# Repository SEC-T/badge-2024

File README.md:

# SEC-T 0x10sion Music Synthesizer Badge kit

The SEC-T 0x10sion Music Synthesizer Badge is a kit that attendees of SEC-T 0x10sion 2024 must solder together.
It is an Arduino-compatible music synthesizer kit with:
* a touch keyboard
* built-in speaker/amp
* audio output jack (for high-quality audio)
* 5 programmable RGB LEDs

It is designed to be perfect for total beginners to learn to solder and complete successfully.

The SEC-T Synth Badge comes with a pre-programmed music synthesizer that makes way cool sounds and music and noise.
Once soldering is completed, the SEC-T Synth Badge is a really nice, portable, performing musical instrument!

The SEC-T Synth Badge kit is based on the ArduTouch music synthesizer kit by Mitch Altman / Cornfield Electronics,
which is fully Open Hardware, with a CC BY-SA 4.0 license.

The SEC-T Synth Badge makes use of a modified ArduTouch library, which is available for
programming in more super nice synthesizer features, and for making your own synthesizers.
The library comes with examples (with more to come) that serve as a nice tutorial
on how to create your own SEC-T Synth Badge synthesizers (which are Arduino sketches).

The SEC-T Synth Badge is really just an Arduino Uno clone
with the features listed above, a couple of extra buttons, and a four of pots (for playing music and controlling the sounds).
The ArduTouch Arduino Library is where the real magic comes from!

For those who want to learn more, the documentation teaches the basics of Digital Signal Processing for audio generation.

The SEC-T Synth Badge kit is fully Open Hardware, with a CC BY-SA 4.0 license.

---
## Assembly Instructions (with re-programming how-to)

_Click on the image below to open a PDF file with detailed instructions on how to assemble your SEC-T 0x10sion Music Synthesizer Badge (which also includes a how-to for re-programming your Synth Badge with a new Arduino sketch):_  
  
### Part 1 of 2 parts:

### Part 2 of 2 parts:

---
## "Quadrant" Synth Demo Videos

The Synth Badge comes pre-programmed with a synth called __Quadrant__.  
Quadrant is somewhat like a looper.  Every time you play a note it goes into the loop.  You can control the speed of the loop, and you can also make the sound warp (detune) every time through the loop.  
  
There is the default patch for Quadrant, plus 4 presets -- all 5 of these have very different sounds!  
In addition to changing the loop speed and changing the warp-factor, there are many parameters that you can play with, some of which change the sounds in subtle ways, others which change the sounds a lot.  

These demo videos give you a very small taste of the various sounds Quadrant can make. 

___NOTE__:  The demo videos use the prototype version of the SEC-T 0x10sion Music Synthesizer Badge kit._  
There are some differences between the prototype version and the badges at the event.  In particular, the two red buttons are reversed (left and right).  

__Basic Functionality of Quadrant__:  
* At power-up (or after Reset), Quadrant is in the Default Patch
* Single-Click the right red button to go up an octave
* Single-Click the left red button to go down an octave
* Double-Click the right red button and then hit one of the first four lower touch-keys to choose a preset
  * The left-most touch-key is "C" -- Scaffold
  * The next touch-key is "D" -- Farsy
  * "E" -- Teleprompt
  * "F" -- Glacial
  * "G" -- Blur
* Tap the Reset button to get the Default Patch
* The Top Pot controls the Warp-factor
* The Bottom Pot controls the speed of the loop
* Pot A controls tremelo speed
* Pot B controls tremelo depth
* Press-and-hold on the left and right red buttons will make the Red and Blue LEDs light or blink, indicating that the four Pots will now control different parameters.  
  
See the next section, "Quadrant Synth User Guide", for a complete description of all that the Quadrant Synth can do.  
  
### Default Patch (at power-up and after Reset) _-- click on the image below to play the video_

### Preset "C" -- Scaffold _-- click on the image below to play the video_

### Preset "D" -- Farsy _-- click on the image below to play the video_

### Preset "E" -- Teleprompt _-- click on the image below to play the video_

### Preset "F" -- Glacial _-- click on the image below to play the video_

### Preset "G" -- Blur _-- click on the image below to play the video_

---
## Quadrant Synth User Guide

The Synth Badge comes pre-programmed with a synth called __Quadrant__.  Quadrant is a very powerful performing musical instrument.  
_Click on the image below to learn how to play with it:_  

---
## Re-programming the Synth Badge

The Synth Badge can be re-programmed using the free Arduino software (on Windows, Linux, and MacOS).  
The end pages of the [Synth Assembly Instructions](https://github.com/user-attachments/files/16896082/SEC-T_0x10sion_badge_assembly_part_2of2.pdf) explain how to do this.  
To re-program your Synth Badge you will need to use a USB-Serial TTL adapter.  
  
The Synth Badge comes pre-programmed with the __Quadrant__ synth.  
  
There are 8 other synths that were developed for the open hardware_ArduTouch_ project (which the Synth Badge is based on), all of which will work on the SEC-T Synth Badge.  But you should be aware of the following:  
* The Synth Badge has 5 programmable RGB LEDs that the _ArduTouch_ boards do not have.  
* The __Quadrant__ synth sketch (from the Synth Badge's Github) has code for controlling the RGB LEDs, but the _ArduTouch synth sketches do not -- though this functionality can be added by you or others.  
* The Synth Badge does not have touch-keys for "A, A#, or B).
  
All of the documentation for [ArduTouch](https://cornfieldelectronics.com/cfe/projects.php#ardutouch), including the synth sketches, is available on the Cornfield Electronics website:  
https://cornfieldelectronics.com/cfe/projects.php#ardutouch  
  
Here is a list of ArduTouch synths that you can program into your Synth Badge:
* __Thick__: 4-voice sawtooth synth
* __Arpology__: Arpegiating synth
* __Beatitude__: drum sequencer with bass synth
* __Dronetic__: drone-making synth
* __Hocus__: Hammond organ (with Leslie) emulator synth
* __Mantra__: Indian-like percusion/bass/drone/melody synth
* __Xoid__: Digital-noise synth
* __ZapShot__: 8-bit video-game-sound synth

---
## A Note on the (Horrible) User Interface for the Quadrant Synth

As noted in the [Quadrant Synth User Guide](https://github.com/user-attachments/files/16901048/Quadrant_Synth_User_Guide.pdf) (see the "Quadrant Synth User Guide", above), the User Interface is really annoying.  

The following is quoted from the Quadrant Synth User Guide:  
  
&nbsp;&nbsp;&nbsp;&nbsp;&nbsp;&nbsp;_You will be annoyed at the User Interface for this synth.  Sorry about that.  The reason that it is so annoying  
&nbsp;&nbsp;&nbsp;&nbsp;&nbsp;&nbsp;is that there are so few Input/Output pins available on the microcontroller.  There were only enough I/O pins  
&nbsp;&nbsp;&nbsp;&nbsp;&nbsp;&nbsp;for 2 LED indicators, 2 Buttons, and 4 Pots._  
  
&nbsp;&nbsp;&nbsp;&nbsp;&nbsp;&nbsp;_I had to come up with a way to control all of the functionality of the Quadrant synth with only the above inputs  
&nbsp;&nbsp;&nbsp;&nbsp;&nbsp;&nbsp;and outputs.  The result is not ideal.  Yet, with some practice, you will find that your Quadrant synth is quite  
&nbsp;&nbsp;&nbsp;&nbsp;&nbsp;&nbsp;usable as a really nice performing musical instrument._  
  
&nbsp;&nbsp;&nbsp;&nbsp;&nbsp;&nbsp;_FYI:  I chose this microcontroller to be the same as the one used in an Arduino Uno:  ATmega328.  This was so  
&nbsp;&nbsp;&nbsp;&nbsp;&nbsp;&nbsp;that the project would be easy to use for beginners, easy to learn for beginners, easy to hack, and also as  
&nbsp;&nbsp;&nbsp;&nbsp;&nbsp;&nbsp;inexpensive as possible._  

---
## Schematic Diagram

_Click on the thumbnail below to to see the PDF file:_

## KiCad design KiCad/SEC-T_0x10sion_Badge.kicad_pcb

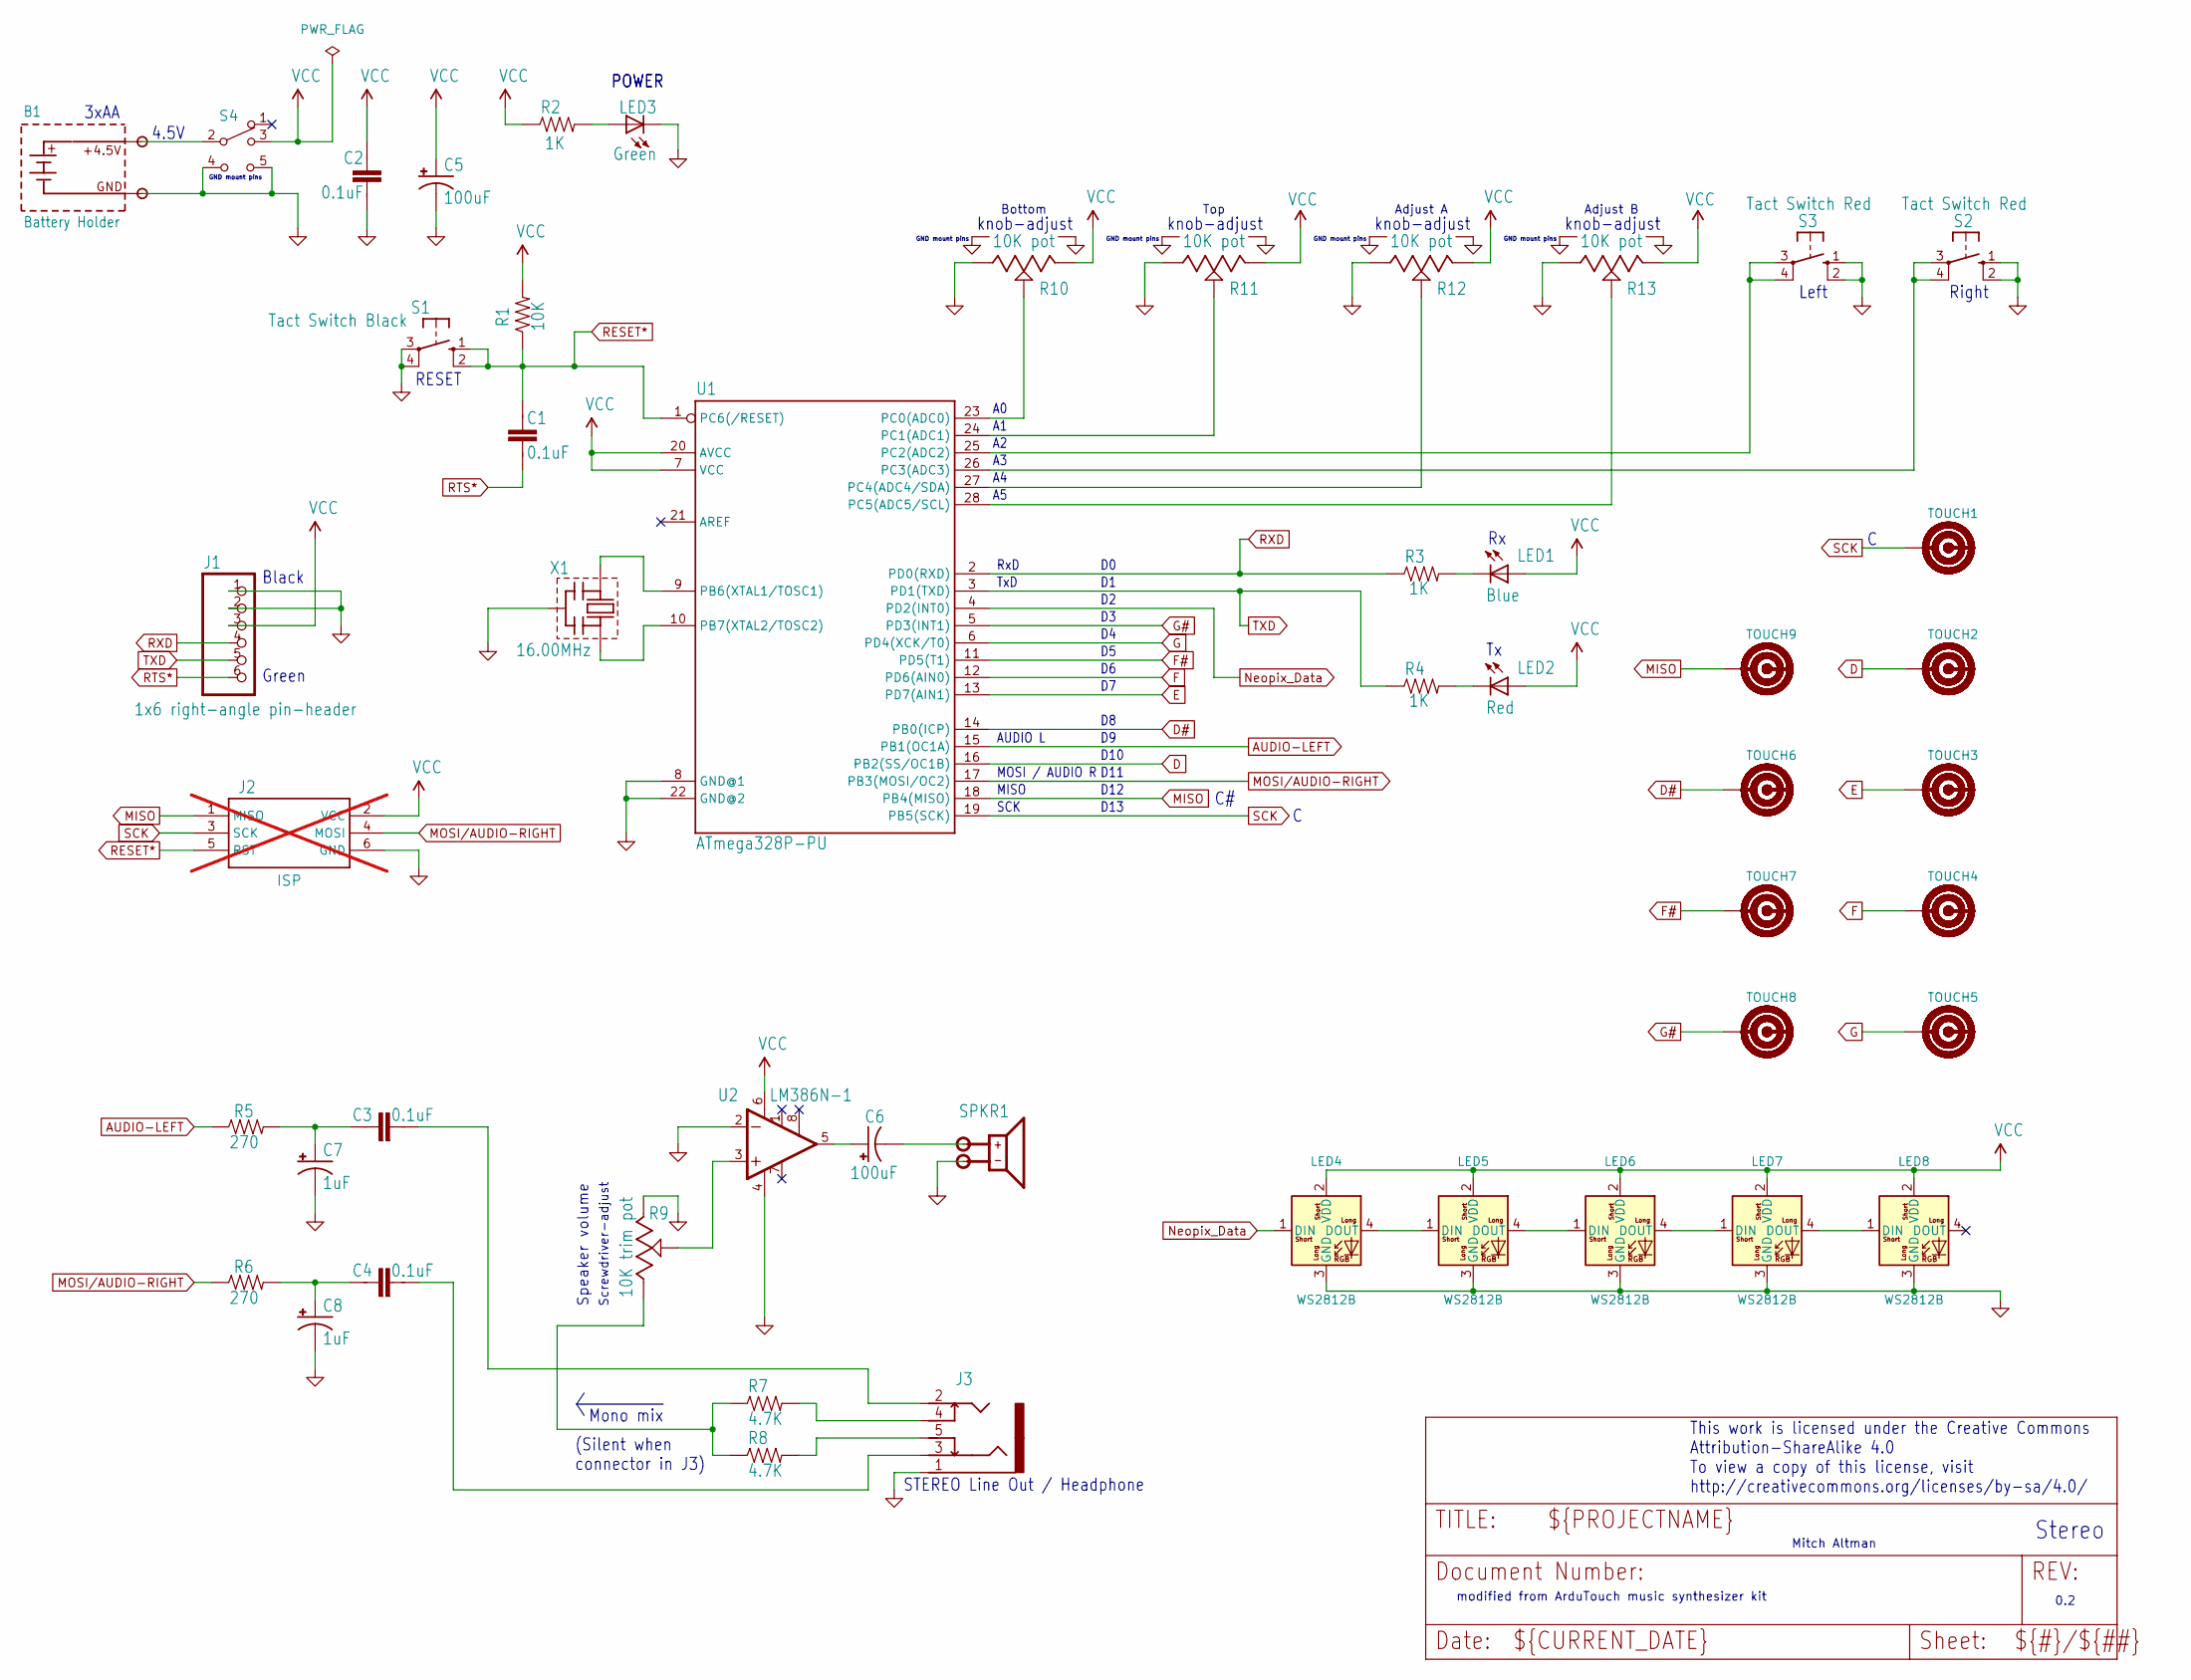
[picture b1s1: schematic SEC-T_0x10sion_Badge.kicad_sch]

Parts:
B1: Battery Holder; BatteryHolder_Eagle_Plastic_Devices_3xAA; Part # Eagle Plastic 12BH331P-GR
C1, C2, C3, C4: 0.1uF; Cap_Kemet_2.54_MLCC_through-hole; Part # KEMET C320C104M5R5TA
C5, C6: 100uF; Cap_Wurth_Electrolytic_100uF; Part # Wurth 860010473007
C7, C8: 1uF; Cap_Rubycon_Electrolytic_1uF; Part # Rubycon 450PK1MEFC6.3X11
J1: 1x6 right-angle pin-header; 1x06-pin-header_2.54mm_spacing; Part # Amphenol 10129379-906004BLF
J2: ISP; 2x3_-pin-header_2.54mm_spacing; Part # {not stuffed); not fitted
J3: STEREO-AUDIO-3.5MM-SWITCHED; 3.5mm_CUI_SJ1-3525NG_Horizontal; Part # CIU Devices SJ1-3525NG-GR
LED1: Blue; LED5MM; Part # Wurth 151051BS04000
LED2: Red; LED5MM; Part # Wurth 151051SS04000
LED3: Green; LED5MM; Part # Wurth 151051VS04000
LED4, LED5, LED6, LED7, LED8: WS2812B; LED_WS2812_5mm_Wide_Pins; Part # SparkFun COM-12986
R1: 10K; Resistor_THT_0.25W; Part # SEI Stackpole CF18JT10K0
R2, R3, R4: 1K; Resistor_THT_0.25W; Part # YAGEO CFR-25JR-52-1K
R5, R6: 270; Resistor_THT_0.25W; Part # YAGEO CFR25SJT-26-270R
R7, R8: 4.7K; Resistor_THT_0.25W; Part # YAGEO CFR25SJT-52A4K7
R9: 10K trim pot; TRIMPOT-Bourns-3306F
R10, R11, R12, R13: 10K pot; Potentiometer_TT_P120PK; Part # TT Electronics P120PK-Y25BR10K
S1: Tact Switch Black; TACTILE_SWITCH_6.3MM; Part # CUI Devices TS02-66-60-BK-260-LCR-D
S2, S3: Tact Switch Red; TACTILE_SWITCH_6.3MM; Part # Diptronics DTS-65R-V
S4: SPST; C&K_SPST_OS102011MS2QS1; Part # C&K OS102011MS2QS1
SPKR1: SPEAKER-TERMINALS; Part # DONGGUAN INGHAI ELECTRONICS GSPK2003TN-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
TOUCH1, TOUCH2, TOUCH3, TOUCH4, TOUCH5, TOUCH6, TOUCH7, TOUCH8, TOUCH9: PCB-TOUCHPAD
U1: ATmega328P-PU; DIP-28_W7.62mm_Socket
U2: LM386N-1; DIP-8_W7.62mm; Part # Texas Instruments LM386N-1/NOPB
X1: 16.00MHz; CERM_OSC_16MHz; Part # Murata CSTLS16M0X53-B0

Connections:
AUDIO-LEFT: R5.P$1 (1), U1.15 (PB1(OC1A))
D: TOUCH2.1, U1.16 (PB2(SS/OC1B))
D#: TOUCH6.1, U1.14 (PB0(ICP))
E: TOUCH3.1, U1.13 (PD7(AIN1))
F: TOUCH4.1, U1.12 (PD6(AIN0))
F#: TOUCH7.1, U1.11 (PD5(T1))
G: TOUCH5.1, U1.6 (PD4(XCK/T0))
G#: TOUCH8.1, U1.5 (PD3(INT1))
GND: B1.-, C2.2, C5.-, C7.-, C8.-, J1.1, J1.2, J2.6 (GND), J3.1 (GND), LED3.K (C), LED4.3 (GND), LED5.3 (GND), LED6.3 (GND), LED7.3 (GND), LED8.3 (GND), R9.1 (CCW), R10.1 (CCW), R10.GND, R11.1 (CCW), R11.GND, R12.1 (CCW), R12.GND, R13.1 (CCW), R13.GND, S1.3, S1.4, S2.1, S2.2, S3.1, S3.2, S4.4 (GND), S4.5 (GND), SPKR1.-, U1.8 (GND@1), U1.22 (GND@2), U2.2 (-IN), U2.4 (V-), X1.P$2 (GND)
MISO: J2.1 (MISO), TOUCH9.1, U1.18 (PB4(MISO))
MOSI/AUDIO-RIGHT: J2.4 (MOSI), R6.P$1 (1), U1.17 (PB3(MOSI/OC2))
Neopix_Data: LED4.1 (DIN), U1.4 (PD2(INT0))
unnamed: B1.+, S4.2
unnamed: C6.-, SPKR1.+
unnamed: C4.2, J3.3 (Ring)
unnamed: J3.5 (Ring_Switch), R8.P$2 (2)
unnamed: C3.2, J3.2 (Tip)
unnamed: J3.4 (Tip_Switch), R7.P$2 (2)
unnamed: LED1.K (C), R3.P$2 (2)
unnamed: LED2.K (C), R4.P$2 (2)
unnamed: LED4.4 (DOUT), LED5.1 (DIN)
unnamed: LED5.4 (DOUT), LED6.1 (DIN)
unnamed: LED6.4 (DOUT), LED7.1 (DIN)
unnamed: LED7.4 (DOUT), LED8.1 (DIN)
unnamed: LED3.A, R2.P$2 (2)
unnamed: C3.1, C7.+, R5.P$2 (2)
unnamed: C4.1, C8.+, R6.P$2 (2)
unnamed: R7.P$1 (1), R8.P$1 (1), R9.3 (CW)
unnamed: R9.2 (Wiper), U2.3 (+IN)
unnamed: R10.2 (Wiper), U1.23 (PC0(ADC0))
unnamed: R11.2 (Wiper), U1.24 (PC1(ADC1))
unnamed: R12.2 (Wiper), U1.27 (PC4(ADC4/SDA))
unnamed: R13.2 (Wiper), U1.28 (PC5(ADC5/SCL))
unnamed: U1.9 (PB6(XTAL1/TOSC1)), X1.P$1 (IN)
unnamed: U1.10 (PB7(XTAL2/TOSC2)), X1.P$3 (OUT)
unnamed: S3.3, S3.4, U1.25 (PC2(ADC2))
unnamed: S2.3, S2.4, U1.26 (PC3(ADC3))
unnamed: C6.+, U2.5 (OUT)
RESET*: C1.1, J2.5 (RST), R1.P$1 (1), S1.1, S1.2, U1.1 (PC6(/RESET))
RTS*: C1.2, J1.6
RXD: J1.4, R3.P$1 (1), U1.2 (PD0(RXD))
SCK: J2.3 (SCK), TOUCH1.1, U1.19 (PB5(SCK))
TXD: J1.5, R4.P$1 (1), U1.3 (PD1(TXD))
VCC: C2.1, C5.+, J1.3, J2.2 (VCC), LED1.A, LED2.A, LED4.2 (VDD), LED5.2 (VDD), LED6.2 (VDD), LED7.2 (VDD), LED8.2 (VDD), R1.P$2 (2), R2.P$1 (1), R10.3 (CW), R11.3 (CW), R12.3 (CW), R13.3 (CW), S4.3, U1.7 (VCC), U1.20 (AVCC), U2.6 (V+)

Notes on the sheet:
GND mount pins
Top
Bottom
RESET
Screwdriver-adjust
knob-adjust
RxD
This work is licensed under the Creative Commons Attribution-ShareAlike 4.0 To view a copy of this license, visit http://creativecommons.org/licenses/by-sa/4.0/
4.5V
D10
D13
Adjust A
D11
Mono mix
modified from ArduTouch music synthesizer kit
Adjust B
Black
MOSI / AUDIO R
POWER
3xAA
MISO
Green
AUDIO L
Right
D12
0.2
Stereo
STEREO Line Out / Headphone
TxD
Left
Speaker volume
(Silent when connector in J3)
Mitch Altman
SCK

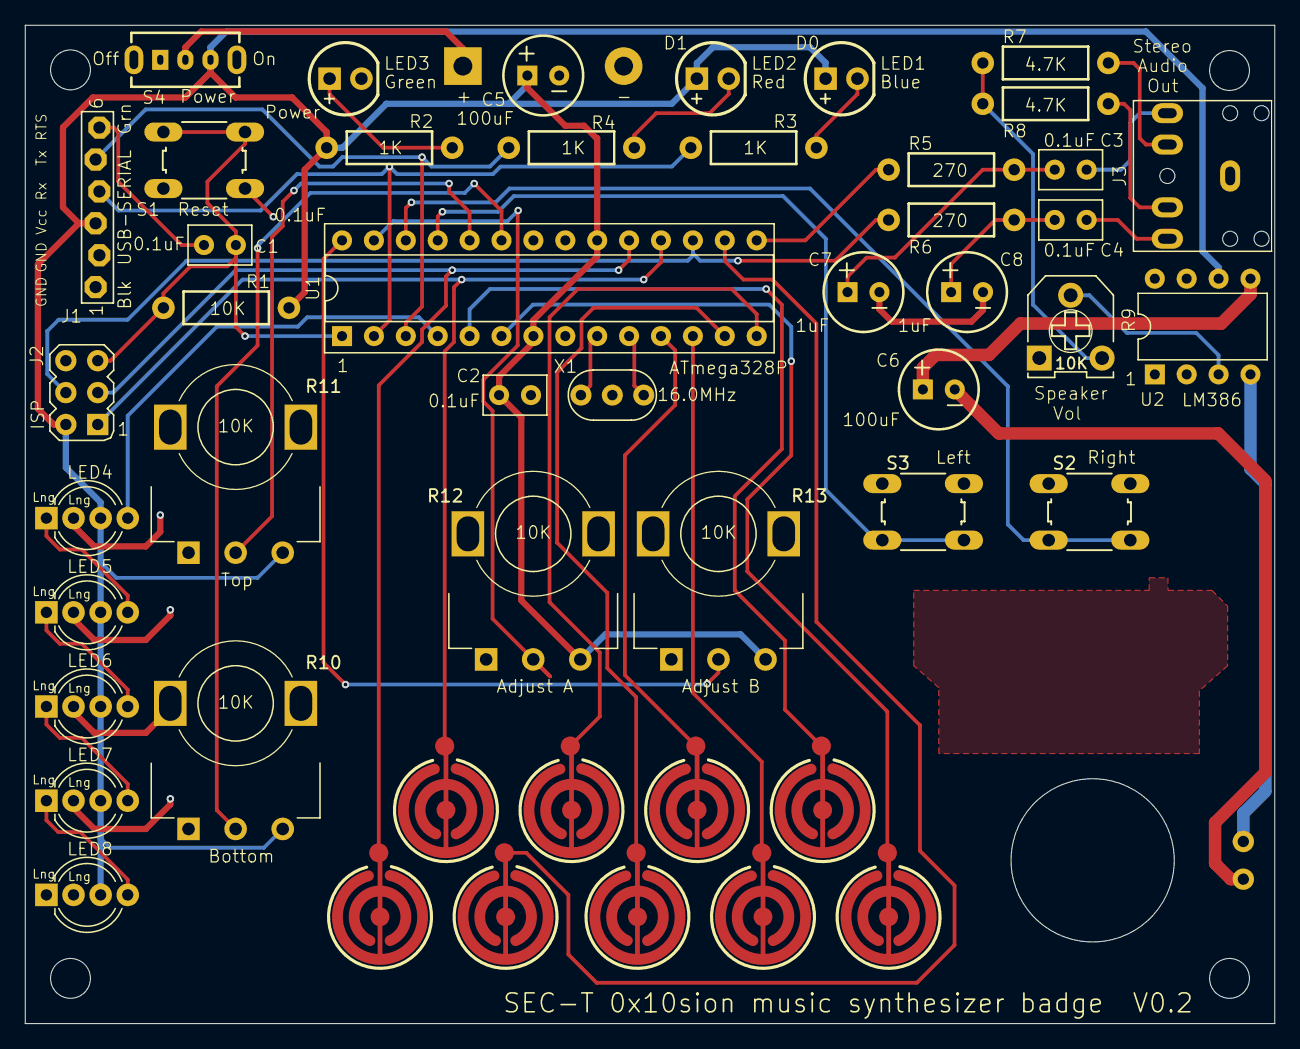
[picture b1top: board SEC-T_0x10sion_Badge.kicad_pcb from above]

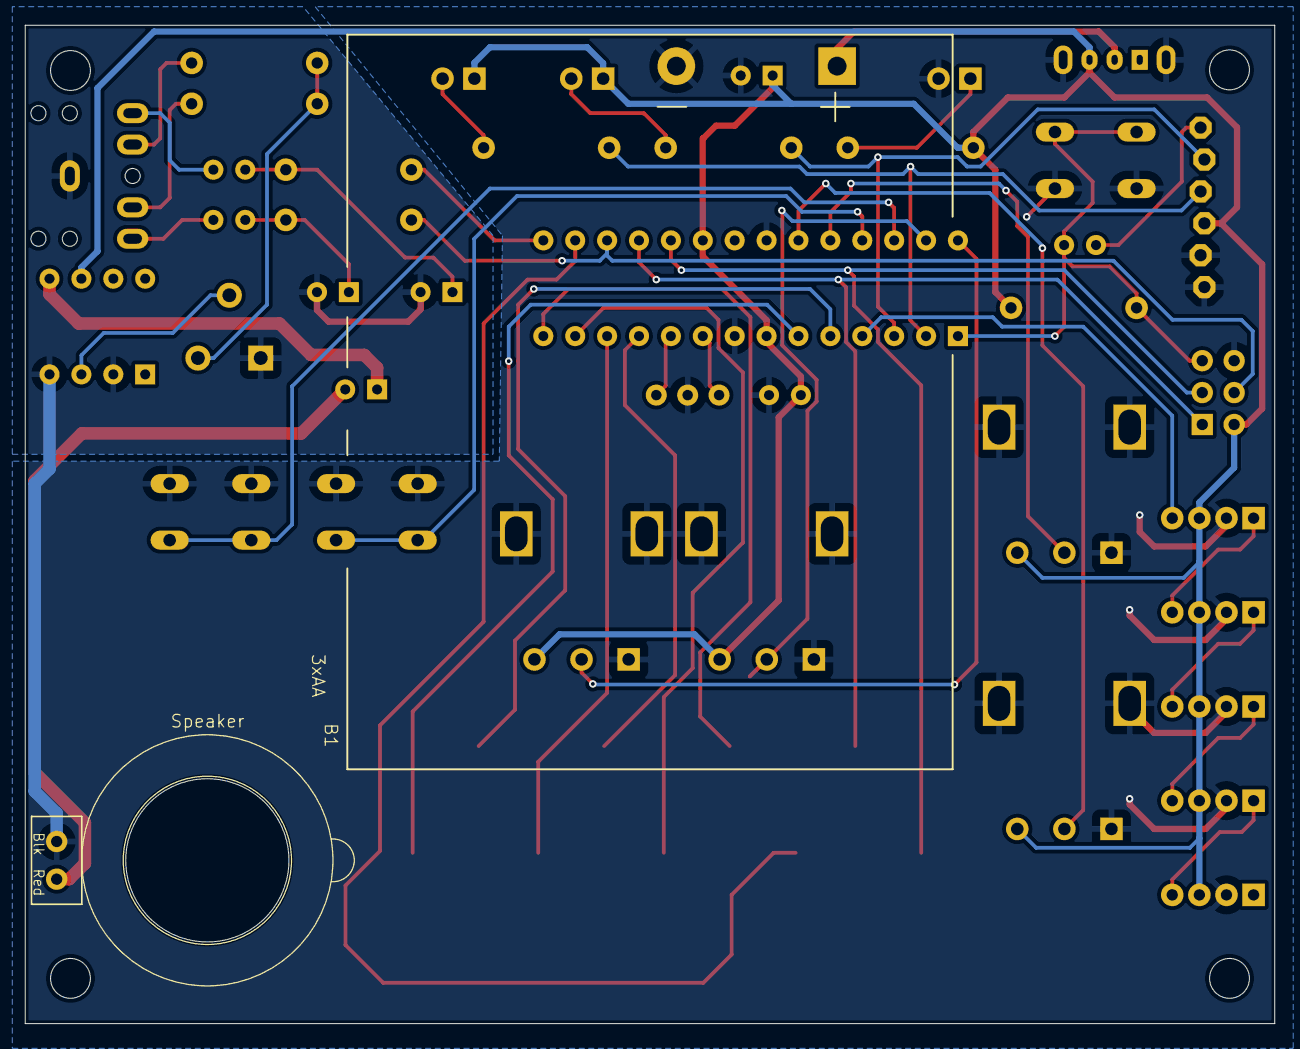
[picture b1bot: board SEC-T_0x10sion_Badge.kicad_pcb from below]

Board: 2 copper layers, 99.5 x 79.5 mm, 54 parts (2 on the bottom side), 44 nets.

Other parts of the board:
@HOLE0, @HOLE1, @HOLE2, @HOLE3: (no value)

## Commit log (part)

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2024-08-29 Add README, License, KiCad files
    Add first draft of README.md, License.md, and the production version of all KiCad source files (SEC-T_0x10sion_Badge v0.2).
2024-09-01 Update README.md
    Added demo video for Preset "F"
2024-09-01 Update README.md
    Add short description for basic functionality of Quadrant synth
2024-09-01 Update README.md
    Added demo videos for all patches
2024-09-03 Update README.md
    Updated Default Patch demo video, added Preset "G" demo video
2024-09-03 BOM, Arduino library, Quadrant sketch
    Add BOM, ArduTouch Arduino library, Quadrant sketch
2024-09-03 Update README.md
    Added how to get "G" (Blur) and Default Patch
2024-09-04 Create SEC-T_0x10sion_badge_assembly.pdf
    Add Assembly Instructions / Re-programming how-to
2024-09-05 Update README.md
    Added Assembly instructions (with re-programming how-to)
2024-09-05 Update comments in Quadrant sketch, add Quadrant User Guide
    * Update comments in Quadrant sketch to fix a couple of errors and add some info on ArduTouch vs SEC-T Synth Badge.
    * Add Quadrant User Guide.
2024-09-05 Update README.md
    Added Quadrant Synth User Guide
2024-09-05 updated program name in Quadrant sketch
2024-09-06 add schematic
2024-09-07 Update README.md
    Added schematic diagram
2024-09-07 Update README.md
    add section for Re-programming the Synth Badge
2024-09-07 Update README.md
    add Note on UI
2024-09-13 add CTF challenge hex file
2025-09-12 Update SEC-T_0x10sion_badge_assembly.pdf
    Update Assembly Instructions to use Kester K100LD Rosin solder.
